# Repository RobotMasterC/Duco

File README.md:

# Duco

Duco is a low profile split keyboard that has extra keys for macros and uses ZMK firmware

It was made for Hack Clubs [Blueprint](https://blueprint.hackclub.com) program!

## Images

### Schematic

### PCB

### Top Case

### Bottom Case

## Firmware

[Repository is here](https://github.com/RobotMasterC/zmk-config)

## BOM
Overall cost: $116.82
| Item  | Quantity | Unit Price | Total Price |
|-------|----------|------------|-------------|
| [XIAO NRF52840](https://www.mouser.com/ProductDetail/Seeed-Studio/102010672?qs=sqEgtWRSLJ0SuHAgTfdO0A%3D%3D) | 2 | 10.4 | 20.8 |
| [Hotswap Socket (10 Pack)](https://www.mouser.com/ProductDetail/Adafruit/5118?qs=TCDPyi3sCW0NahZ3INJp%2FA%3D%3D) | 60 | 2.5 | 15 |
| [Red Choc Switches (10 Pack)](https://chosfox.com/products/kailh-chocs?variant=42514647613634) | 60 | 4.5 | 27 |
| [1N4148 Diodes](https://www.mouser.com/ProductDetail/Diotec-Semiconductor/1N4148W?qs=OlC7AqGiEDmsbkbAeXQtXg%3D%3D) | 56 | 0.045 | 2.7 |
| [PCM12SMTR Switch](https://www.mouser.com/ProductDetail/CK/PCM12SMTR?qs=mfFuHy8STfL3qrPSfCHA7w%3D%3D) | 2| 1.16 | 2.32 |
| [PCB](https://jlcpcb.com)| 5|| 14.8 |
| Case (3D Printed)| 4 | | 0 |
| Keycaps (3D Printed) | 56 || 0|
| Shipping (Mouser)||| 8.49|
| Shipping (JLCPCB)||| 11.99|
| Shipping (ChosFox)||| 6.8|
| Tarrif Estimate (Mouser)||| 6.27|
|||||
| Overall Cost||| 116.17|
| Grant Needed||| 89.38|
| (I will pay for the PCB to let this fit into tier 3) ||||

### Cart Screenshots

| JLCPCB | ChosFox | Mouser |
|--------|---------|--------|
| || |

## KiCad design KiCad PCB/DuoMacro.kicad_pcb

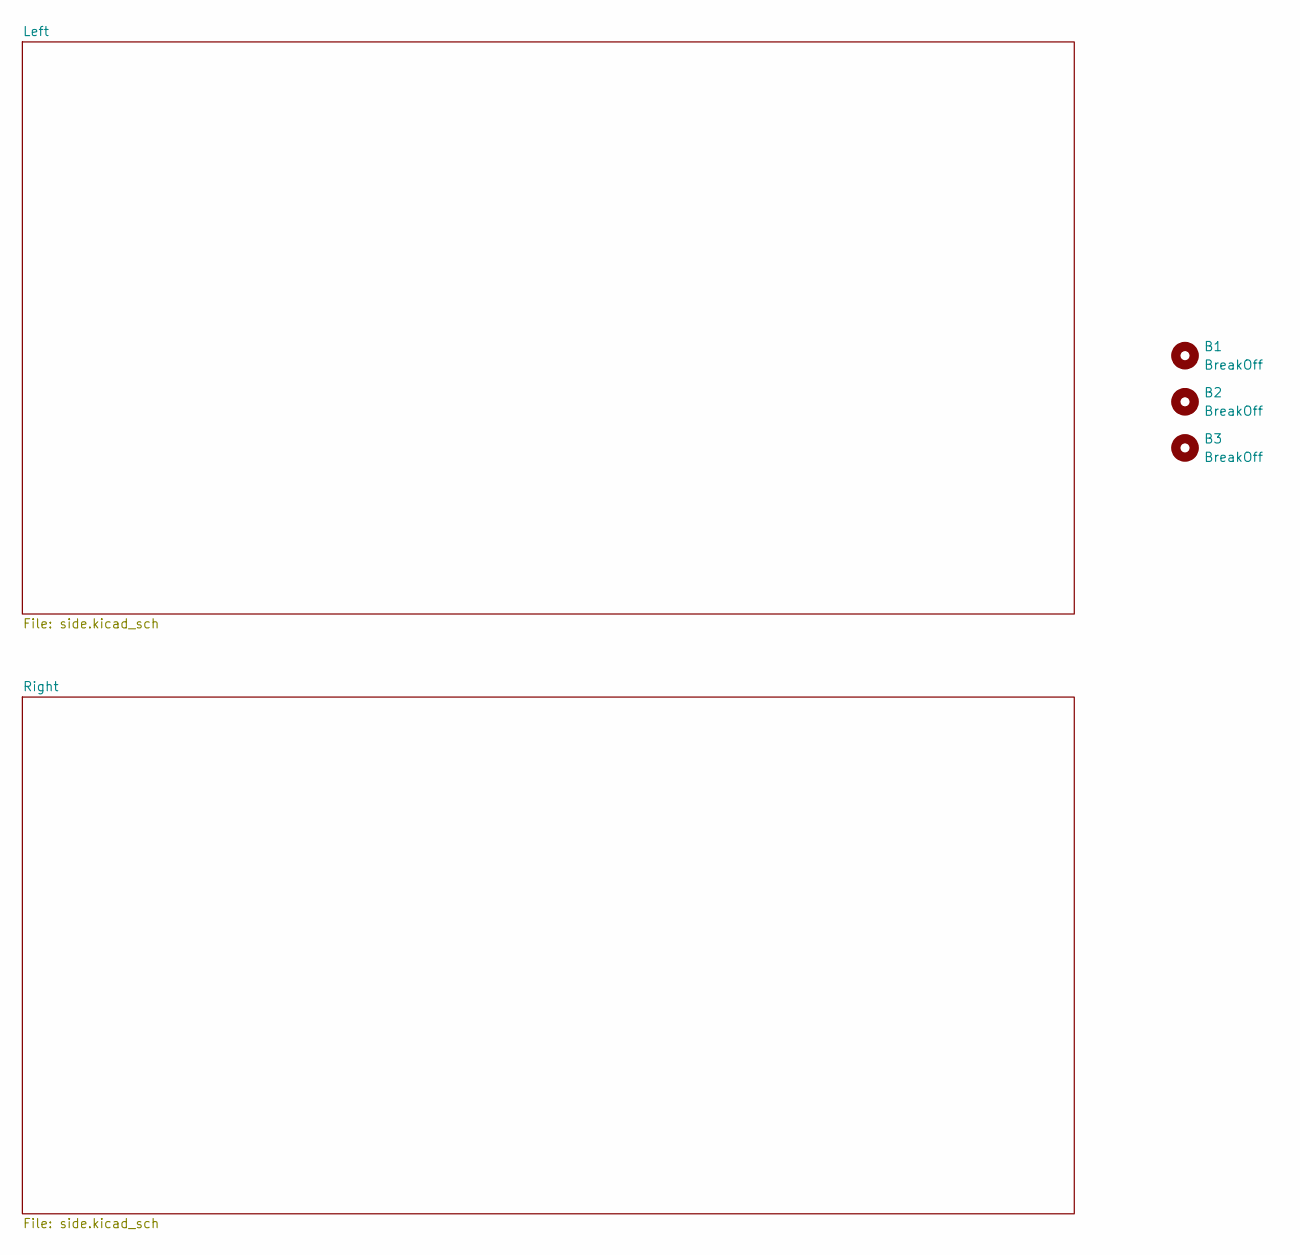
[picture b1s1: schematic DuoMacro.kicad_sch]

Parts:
B1, B2, B3: BreakOff; MouseBite-Slot_2.0x2.0mm_outset_D0.5mm_P0.85mm_3h

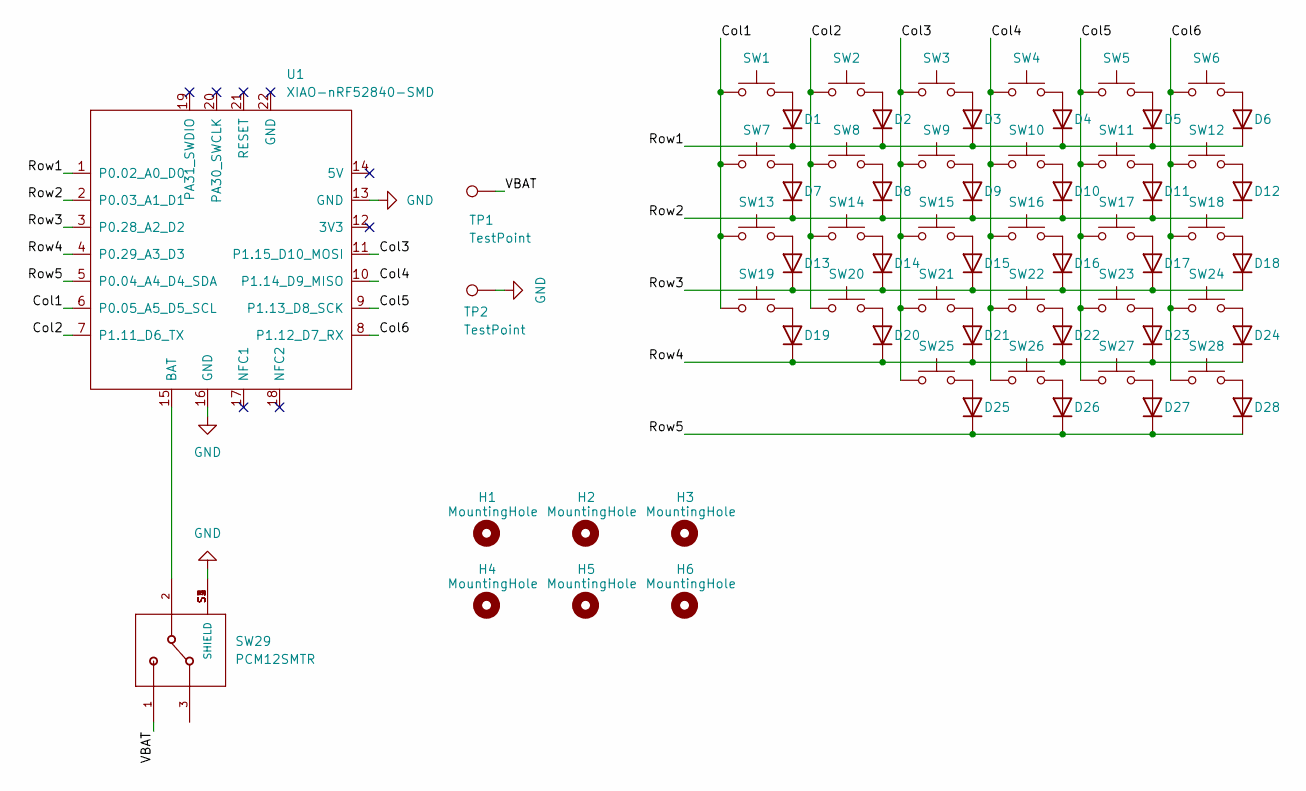
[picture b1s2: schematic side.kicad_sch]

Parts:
D1, D2, D3, D4, D5, D6, D7, D8, D9, D10, D11, D12, D13, D14, D15, D16, D17, D18, D19, D20, D21, D22, D23, D24, D25, D26, D27, D28: D_SOD-123
H1, H2, H3, H4, H5, H6: MountingHole; MountingHole_2.2mm_M2_Better
SW1, SW2, SW3, SW4, SW5, SW6, SW7, SW8, SW9, SW10, SW11, SW12, SW13, SW14, SW15, SW16, SW17, SW18, SW19, SW20, SW21, SW22, SW23, SW24, SW25, SW26, SW27: SW_Push; SW_choc_v1_HS_CPG135001S30_1u
SW28: SW_Push; SW_choc_v1_HS_CPG135001S30_1.5u
SW29: PCM12SMTR; SW_PCM12SMTR
TP1, TP2: TestPoint; TestPoint_Pad_D2.5mm
U1: XIAO-nRF52840-SMD; modified-XIAO-nRF52840-SMD

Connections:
/Left/Col1: SW1.1, SW7.1, SW13.1, SW19.1, U1.6 (P0.05_A5_D5_SCL)
/Left/Col2: SW2.1, SW8.1, SW14.1, SW20.1, U1.7 (P1.11_D6_TX)
/Left/Col3: SW3.1, SW9.1, SW15.1, SW21.1, SW25.1, U1.11 (P1.15_D10_MOSI)
/Left/Col4: SW4.1, SW10.1, SW16.1, SW22.1, SW26.1, U1.10 (P1.14_D9_MISO)
/Left/Col5: SW5.1, SW11.1, SW17.1, SW23.1, SW27.1, U1.9 (P1.13_D8_SCK)
/Left/Col6: SW6.1, SW12.1, SW18.1, SW24.1, SW28.1, U1.8 (P1.12_D7_RX)
/Left/Row1: D1.1 (K), D2.1 (K), D3.1 (K), D4.1 (K), D5.1 (K), D6.1 (K), U1.1 (P0.02_A0_D0)
/Left/Row2: D7.1 (K), D8.1 (K), D9.1 (K), D10.1 (K), D11.1 (K), D12.1 (K), U1.2 (P0.03_A1_D1)
/Left/Row3: D13.1 (K), D14.1 (K), D15.1 (K), D16.1 (K), D17.1 (K), D18.1 (K), U1.3 (P0.28_A2_D2)
/Left/Row4: D19.1 (K), D20.1 (K), D21.1 (K), D22.1 (K), D23.1 (K), D24.1 (K), U1.4 (P0.29_A3_D3)
/Left/Row5: D25.1 (K), D26.1 (K), D27.1 (K), D28.1 (K), U1.5 (P0.04_A4_D4_SDA)
/Left/VBAT: SW29.1, TP1.1
GND: SW29.S1 (SHIELD), SW29.S2 (SHIELD), SW29.S3 (SHIELD), SW29.S4 (SHIELD), TP2.1, U1.13 (GND), U1.16 (GND); also elsewhere on the board
unnamed: D1.2 (A), SW1.2
unnamed: D2.2 (A), SW2.2
unnamed: D3.2 (A), SW3.2
unnamed: D4.2 (A), SW4.2
unnamed: D5.2 (A), SW5.2
unnamed: D6.2 (A), SW6.2
unnamed: D7.2 (A), SW7.2
unnamed: D8.2 (A), SW8.2
unnamed: D9.2 (A), SW9.2
unnamed: D10.2 (A), SW10.2
unnamed: D11.2 (A), SW11.2
unnamed: D12.2 (A), SW12.2
unnamed: D13.2 (A), SW13.2
unnamed: D14.2 (A), SW14.2
unnamed: D15.2 (A), SW15.2
unnamed: D16.2 (A), SW16.2
unnamed: D17.2 (A), SW17.2
unnamed: D18.2 (A), SW18.2
unnamed: D19.2 (A), SW19.2
unnamed: D20.2 (A), SW20.2
unnamed: D21.2 (A), SW21.2
unnamed: D22.2 (A), SW22.2
unnamed: D23.2 (A), SW23.2
unnamed: D24.2 (A), SW24.2
unnamed: D25.2 (A), SW25.2
unnamed: D26.2 (A), SW26.2
unnamed: D27.2 (A), SW27.2
unnamed: D28.2 (A), SW28.2
unnamed: SW29.2, U1.15 (BAT)

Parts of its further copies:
D29, D30, D31, D32, D33, D34, D35, D36, D37, D38, D39, D40, D41, D42, D43, D44, D45, D46, D47, D48, D49, D50, D51, D52, D53, D54, D55, D56: D_SOD-123
SW30, SW31, SW32, SW33, SW34, SW35, SW36, SW37, SW38, SW39, SW40, SW41, SW42, SW43, SW44, SW45, SW46, SW47, SW48, SW49, SW50, SW51, SW52, SW53, SW54, SW55, SW56: SW_Push; SW_choc_v1_HS_CPG135001S30_1u
SW57: SW_Push; SW_choc_v1_HS_CPG135001S30_1.5u
SW58: PCM12SMTR; SW_PCM12SMTR
TP3, TP4: TestPoint; TestPoint_Pad_D2.5mm
U2: XIAO-nRF52840-SMD; modified-XIAO-nRF52840-SMD

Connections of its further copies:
/Right/Col1: SW30.1, SW36.1, SW42.1, SW48.1, U2.6 (P0.05_A5_D5_SCL)
/Right/Col2: SW31.1, SW37.1, SW43.1, SW49.1, U2.7 (P1.11_D6_TX)
/Right/Col3: SW32.1, SW38.1, SW44.1, SW50.1, SW54.1, U2.11 (P1.15_D10_MOSI)
/Right/Col4: SW33.1, SW39.1, SW45.1, SW51.1, SW55.1, U2.10 (P1.14_D9_MISO)
/Right/Col5: SW34.1, SW40.1, SW46.1, SW52.1, SW56.1, U2.9 (P1.13_D8_SCK)
/Right/Col6: SW35.1, SW41.1, SW47.1, SW53.1, SW57.1, U2.8 (P1.12_D7_RX)
/Right/Row1: D29.1 (K), D30.1 (K), D31.1 (K), D32.1 (K), D33.1 (K), D34.1 (K), U2.1 (P0.02_A0_D0)
/Right/Row2: D35.1 (K), D36.1 (K), D37.1 (K), D38.1 (K), D39.1 (K), D40.1 (K), U2.2 (P0.03_A1_D1)
/Right/Row3: D41.1 (K), D42.1 (K), D43.1 (K), D44.1 (K), D45.1 (K), D46.1 (K), U2.3 (P0.28_A2_D2)
/Right/Row4: D47.1 (K), D48.1 (K), D49.1 (K), D50.1 (K), D51.1 (K), D52.1 (K), U2.4 (P0.29_A3_D3)
/Right/Row5: D53.1 (K), D54.1 (K), D55.1 (K), D56.1 (K), U2.5 (P0.04_A4_D4_SDA)
/Right/VBAT: SW58.1, TP3.1
GND: SW58.S1 (SHIELD), SW58.S2 (SHIELD), SW58.S3 (SHIELD), SW58.S4 (SHIELD), TP4.1, U2.13 (GND), U2.16 (GND); also elsewhere on the board
unnamed: D29.2 (A), SW30.2
unnamed: D30.2 (A), SW31.2
unnamed: D31.2 (A), SW32.2
unnamed: D32.2 (A), SW33.2
unnamed: D33.2 (A), SW34.2
unnamed: D34.2 (A), SW35.2
unnamed: D35.2 (A), SW36.2
unnamed: D36.2 (A), SW37.2
unnamed: D37.2 (A), SW38.2
unnamed: D38.2 (A), SW39.2
unnamed: D39.2 (A), SW40.2
unnamed: D40.2 (A), SW41.2
unnamed: D41.2 (A), SW42.2
unnamed: D42.2 (A), SW43.2
unnamed: D43.2 (A), SW44.2
unnamed: D44.2 (A), SW45.2
unnamed: D45.2 (A), SW46.2
unnamed: D46.2 (A), SW47.2
unnamed: D47.2 (A), SW48.2
unnamed: D48.2 (A), SW49.2
unnamed: D49.2 (A), SW50.2
unnamed: D50.2 (A), SW51.2
unnamed: D51.2 (A), SW52.2
unnamed: D52.2 (A), SW53.2
unnamed: D53.2 (A), SW54.2
unnamed: D54.2 (A), SW55.2
unnamed: D55.2 (A), SW56.2
unnamed: D56.2 (A), SW57.2
unnamed: SW58.2, U2.15 (BAT)

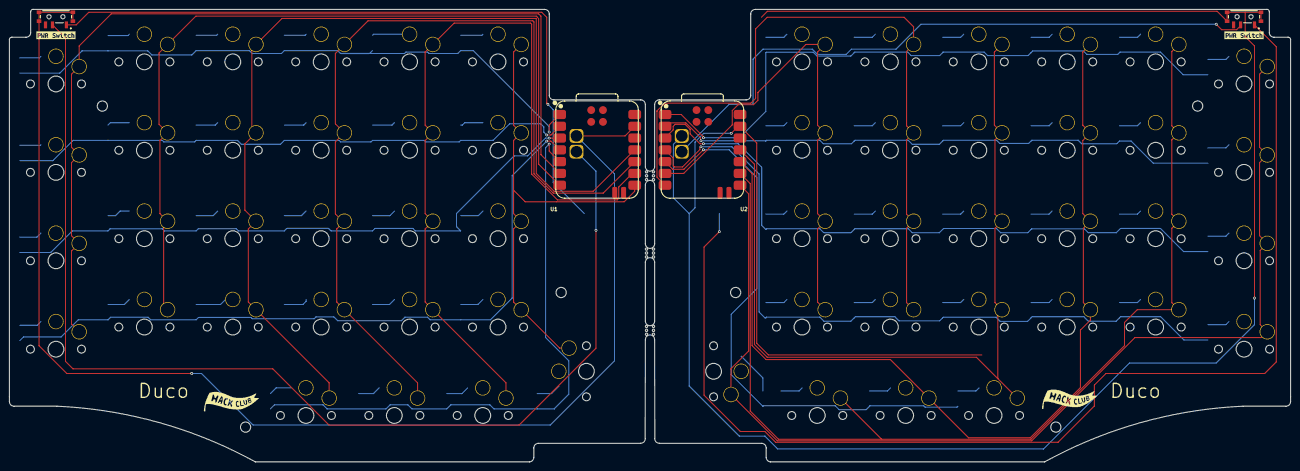
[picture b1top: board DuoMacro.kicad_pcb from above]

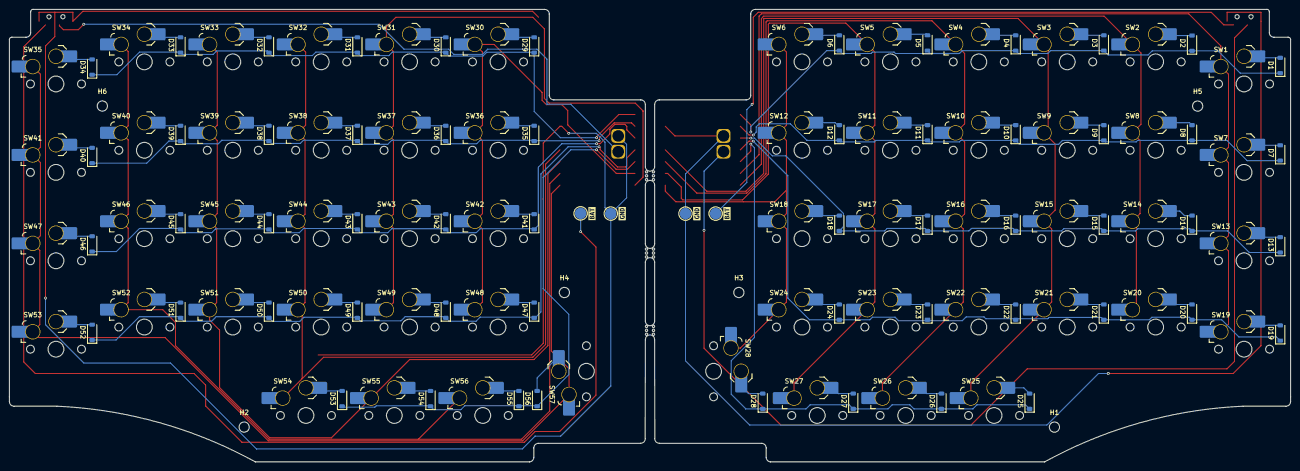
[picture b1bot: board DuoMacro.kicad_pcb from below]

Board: 2 copper layers, 276.0 x 97.5 mm, 135 parts (126 on the bottom side), 83 nets.

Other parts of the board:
kibuzzard-68F124C1, kibuzzard-68F124C1#2: G***; kibuzzard-68F124C1
kibuzzard-68F1247E, kibuzzard-68F1247E#2: G***; kibuzzard-68F1247E
kibuzzard-68F12504, kibuzzard-68F12504#2: G***; kibuzzard-68F12504

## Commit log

2026-03-16 Add all the files
    I know putting this all in one commit is a bad habit, this is all of the files for this project
2026-03-17 Update README.md
    I changed the items that I would be buying myself to be from JLCPCB instead of from mouser with the rest of the stuff to make the buying process easier
2026-03-17 Add images and files for the case
2026-03-17 Update README with images
2026-03-24 Final Updates
2026-03-24 Final Updated
    I needed to add one more line
2026-03-25 Add Cart Screenshots
2026-03-25 Update Readme
    Added cart screenshots to the readme
2026-03-26 Add Case Image Files
2026-03-26 Add images for the Top and Bottom Case
